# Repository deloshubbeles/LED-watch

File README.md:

# LED Watch

### Objective
To display the time and day of week on multiplexed LEDs with button presses, plus more.

**Other intended functionality (yet to be implemented)**
- Low power sleep mode to conserve power when inactive
- Flash low battery warning LED when battery voltage drops too low
- Display LEDs at different brightnesses depending on time of day or button pressed (e.g., brighter in daylight, dimmer at night)
- Stopwatch
- Countdown timer

### Displaying the time

### Components
- [ATmega328P-MMHR (28-pin VQFN)](https://ww1.microchip.com/downloads/en/DeviceDoc/ATmega48A-PA-88A-PA-168A-PA-328-P-DS-DS40002061B.pdf)
- [M41T62 (8 pin LCC) real time clock](https://www.st.com/resource/en/datasheet/m41t62.pdf)
- 34 multiplexed LEDs (18 red, 12 blue, 4 white)
- CR2016 coin cell battery (~90mAh) and battery holder
- 2 x SPST tactile switches

### Schematic

### PCB layers:

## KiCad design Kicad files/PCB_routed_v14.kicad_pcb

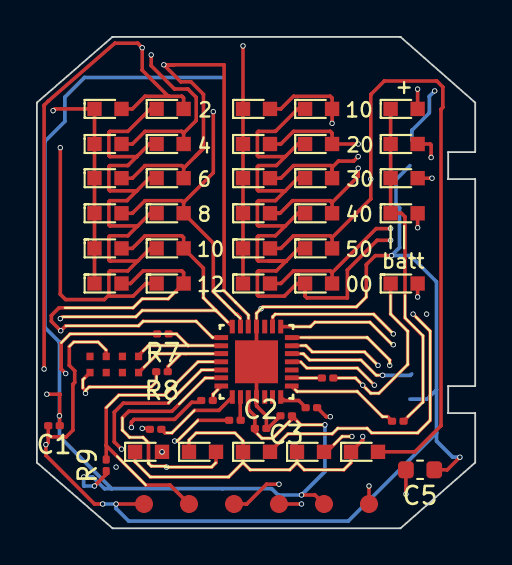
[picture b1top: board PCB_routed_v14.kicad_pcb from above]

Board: 4 copper layers, 24.3 x 27.3 mm, 53 parts (0 on the bottom side), 28 nets.

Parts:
BAT1: CR2016
C1, C3: 100nF; C_0201_0603Metric
C2: 10nF; C_0201_0603Metric
C5: 22uF; C_0603_1608Metric
D1, D2, D3, D4, D5, D6, D7, D8, D9, D10, D11, D12: RED_HR; LED_0603
D13, D14, D15, D16, D17, D18, D19, D20, D21, D22, D23, D24: BLUE_MIN; LED_0603
D25, D26, D27, D28: WHITE_+MIN; LED_0603
D29, D30, D31, D32, D33: RED_DAY; LED_0603
D34: RED_BATT; LED_0603
IC1: M41T62LC6F; LCC90P230X50X80-8N
J1: ICSP-6; ICSP
R1, R2, R6: 2K5; R_0201_0603Metric
R3, R4: 1K5; R_0201_0603Metric
R5: 1K33; R_0201_0603Metric
R7, R8, R9: 10K; R_0201_0603Metric
SW1, SW2: SW_SPST; Switch_SPSTnew
U1: ATmega328-MMH; QFN45P400X400X100-29N

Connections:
/COL_0: R1.1, U1.28
/COL_1: R2.1, U1.1
/COL_2: R3.1, U1.2
/COL_3: R4.1, U1.7
/COL_4: R5.1, U1.8
/COL_5: R6.1, U1.9
/ROW_0: D1.2, D7.2, D13.2, D19.2, D25.2, D29.2, U1.26
/ROW_1: D2.2, D8.2, D14.2, D20.2, D26.2, D30.2, U1.27
/ROW_2: D3.2, D9.2, D15.2, D21.2, D27.2, D31.2, U1.19
/ROW_3: D4.2, D10.2, D16.2, D22.2, D28.2, D32.2, U1.20
/ROW_4: D5.2, D11.2, D17.2, D23.2, D33.2, U1.21
/ROW_5: D6.2, D12.2, D18.2, D24.2, D34.2, U1.22
GND: BAT1.Neg1, C1.2, C2.2, C3.2, C5.1, IC1.3, J1.6, SW1.2, SW2.2, U1.4, U1.18, U1.29
unnamed: BAT1.Pos1, C1.1, C2.1, C3.1, C5.2, IC1.5, J1.2, R7.2, R8.2, R9.1, U1.3, U1.16
unnamed: D1.1, D2.1, D3.1, D4.1, D5.1, D6.1, R1.2
unnamed: D7.1, D8.1, D9.1, D10.1, D11.1, D12.1, R2.2
unnamed: D13.1, D14.1, D15.1, D16.1, D17.1, D18.1, R3.2
unnamed: D19.1, D20.1, D21.1, D22.1, D23.1, D24.1, R4.2
unnamed: D25.1, D26.1, D27.1, D28.1, R5.2
unnamed: D29.1, D30.1, D31.1, D32.1, D33.1, D34.1, R6.2
unnamed: IC1.1, R7.1, U1.23
unnamed: IC1.8, R8.1, U1.24
unnamed: J1.1, U1.14
unnamed: J1.3, U1.15
unnamed: J1.4, U1.13
unnamed: J1.5, R9.2, U1.25
unnamed: SW1.1, U1.11
unnamed: SW2.1, U1.12

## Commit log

2021-10-20 IC component datasheets
2021-10-20 Add files via upload
    PCB layers and circuitboard schematic
2021-11-01 Latest code for LED watch
    Added code for Low power mode and interrupt but yet to test on watch
2021-11-01 Update minute LED calculations to include the remainder
2021-11-05 #2 Fix minute calculation by separating column and row logic
2021-12-04 Add files via upload
    I changed the code to something like the Hackerspace’s Phatbadge so it shows each column at a time, for equally timed intervals. Also changed getting the time in each function (DateTime now = RTC.now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
2021-12-11 Add files via upload
    Moved reading the time (DateTime now = RTC.now();) to the displayTime() function, which has reduced flickering and differences in brightness between columns.
    Only showing remainder minutes for those ending in 5.
2021-12-11 Add files via upload
    Moved reading the time (DateTime now = RTC.now();) into the displayTime() function.
    However, still only showing remainder minutes on those ending in 5
2022-01-07 #4 Use minute % 5 to get minutes 1-4 and 6-9 as positive integers 1-4, then take off one when setting the zero indexed LED
2022-05-18 LED watch running with timer interrupt
2022-05-18 Rename LED_watch.ino to LED_watch_v1.0.ino
2022-05-18 Version 0.1 code
2022-05-18 Version 0.2 code
2022-05-18 Rename LED_watch_v0.2_OLD.ino to LED_watch_v0.2.ino
2022-05-18 Latest code using timer interrupts
2022-05-18 Latest code displaying with timer interrupt
2022-05-18 Rename LED_watch_v0.1.ino to archive/LED_watch_v0.1.ino
2022-05-18 Rename LED_watch_v0.2.ino to archive/LED_watch_v0.2.ino
2022-05-18 Rename LED_watch.ino to LED_watch_TimerInt.ino
2022-10-23 Rename Libraries/README.md to LowPower/README.md
2022-10-28 Commit already
2022-10-28 Moved old .ino file to archive
2022-10-28 Latest watch code
    Using pin change interrupts
2023-06-12 Update README.md
    Moved 'other functionality' above image
